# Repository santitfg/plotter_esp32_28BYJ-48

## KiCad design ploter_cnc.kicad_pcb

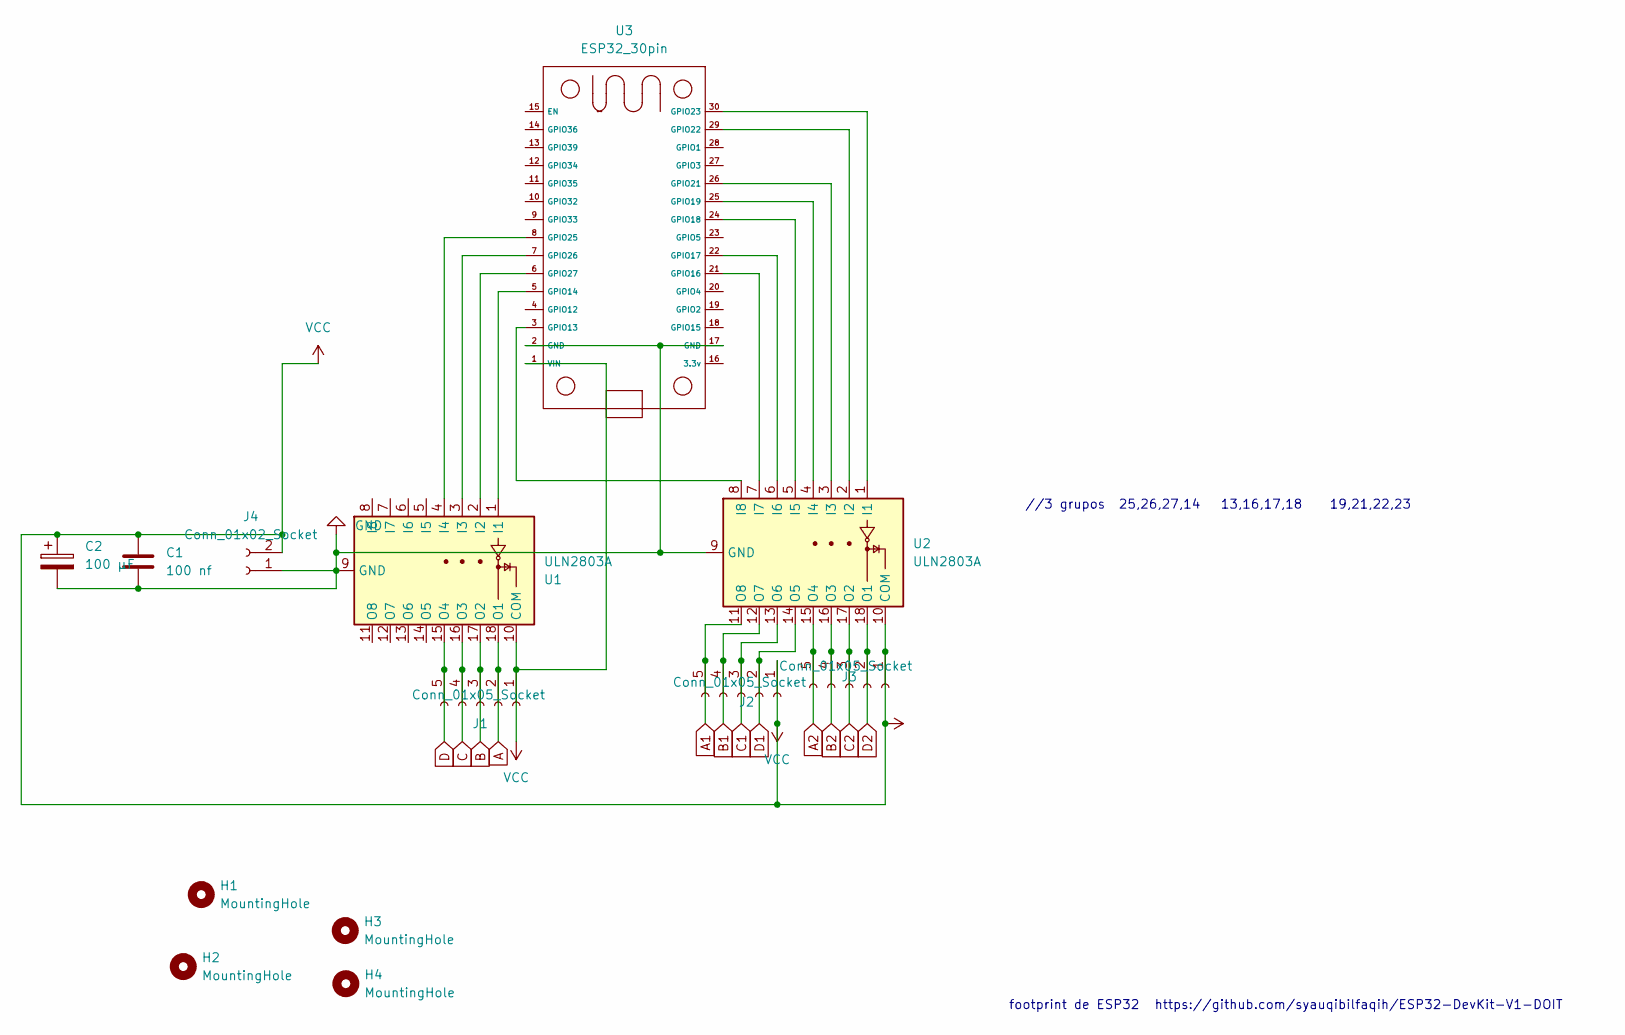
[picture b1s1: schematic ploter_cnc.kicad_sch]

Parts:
C1: 100 nf; C_Disc_D4.3mm_W1.9mm_P5.00mm
C2: 100 µF; CP_Radial_D4.0mm_P2.00mm
H1, H2, H3, H4: MountingHole; MountingHole_2.2mm_M2_DIN965_Pad
J1, J2, J3: Conn_01x05_Socket; Molex_KK-254_AE-6410-05A_1x05_P2.54mm_Vertical
J4: Conn_01x02_Socket; Molex_KK-254_AE-6410-02A_1x02_P2.54mm_Vertical
U1, U2: ULN2803A; DIP-18_W7.62mm_Socket_LongPads
U3: ESP32_30pin

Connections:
A: J1.2, U1.18 (O1)
A2: J3.5, U2.15 (O4)
B: J1.3, U1.17 (O2)
B2: J3.4, U2.16 (O3)
C: J1.4, U1.16 (O3)
C2: J3.3, U2.17 (O2)
D: J1.5, U1.15 (O4)
D2: J3.2, U2.18 (O1)
GND: C1.2, C2.2, J4.1, U1.9 (GND), U2.9 (GND), U3.2 (GND), U3.17 (GND)
unnamed: J2.2, U2.14 (O5)
unnamed: J2.3, U2.13 (O6)
unnamed: J2.4, U2.12 (O7)
unnamed: J2.5, U2.11 (O8)
unnamed: U1.1 (I1), U3.5 (GPIO14)
unnamed: U1.2 (I2), U3.6 (GPIO27)
unnamed: U1.3 (I3), U3.7 (GPIO26)
unnamed: U1.4 (I4), U3.8 (GPIO25)
unnamed: U2.1 (I1), U3.30 (GPIO23)
unnamed: U2.2 (I2), U3.29 (GPIO22)
unnamed: U2.3 (I3), U3.26 (GPIO21)
unnamed: U2.4 (I4), U3.25 (GPIO19)
unnamed: U2.5 (I5), U3.24 (GPIO18)
unnamed: U2.6 (I6), U3.22 (GPIO17)
unnamed: U2.7 (I7), U3.21 (GPIO16)
unnamed: U2.8 (I8), U3.3 (GPIO13)
VCC: C1.1, C2.1, J1.1, J2.1, J3.1, J4.2, U1.10 (COM), U2.10 (COM), U3.1 (VIN)

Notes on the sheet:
https://github.com/syauqibilfaqih/ESP32-DevKit-V1-DOIT
//3 grupos 25,26,27,14 13,16,17,18 19,21,22,23
footprint de ESP32

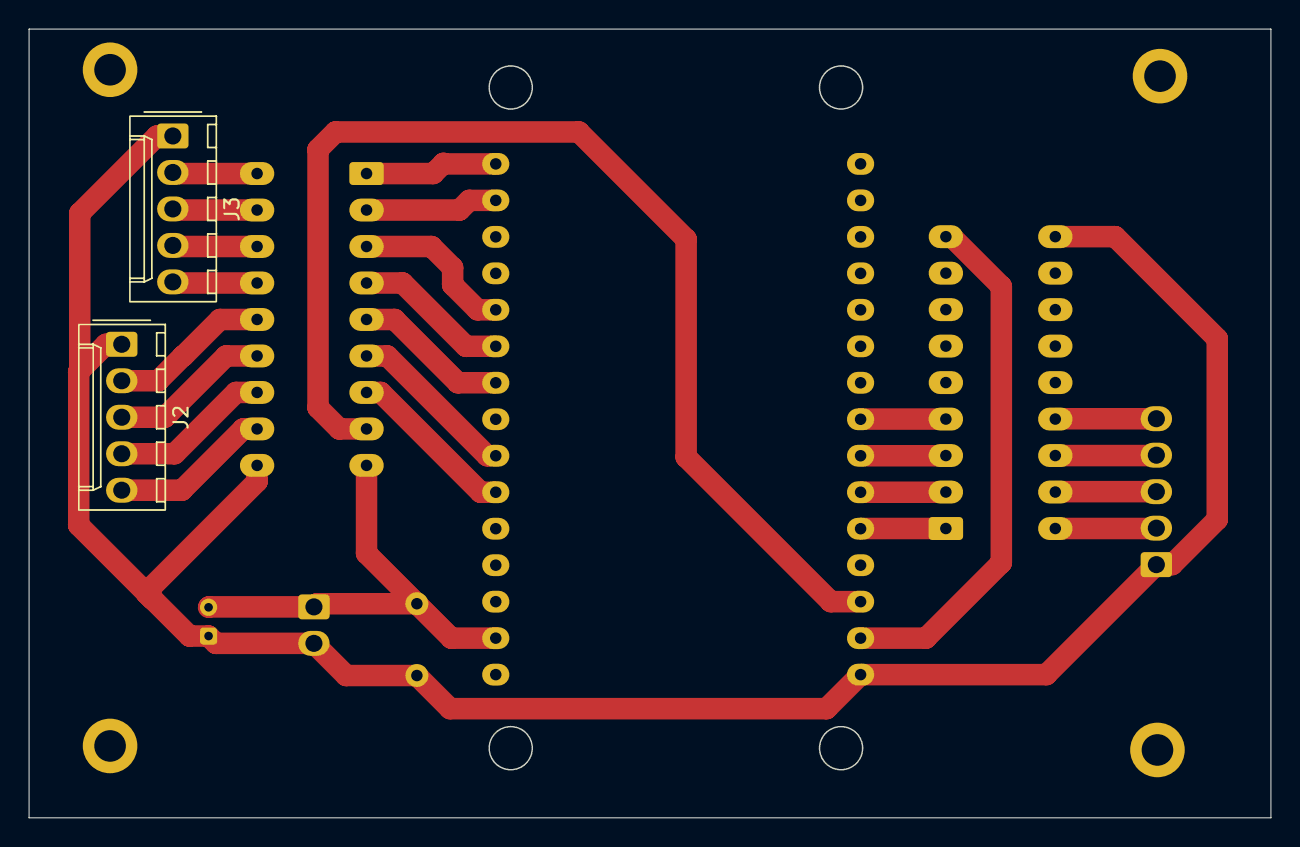
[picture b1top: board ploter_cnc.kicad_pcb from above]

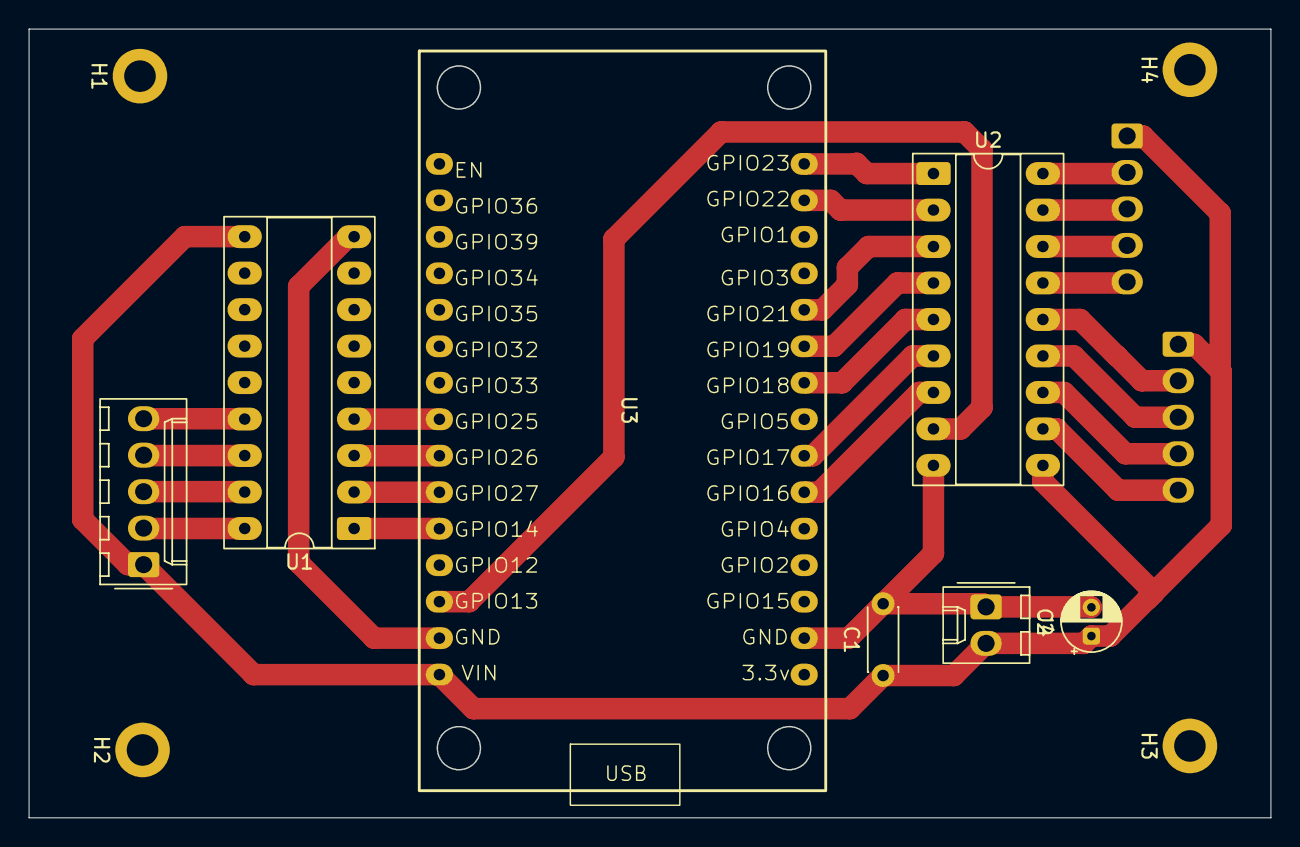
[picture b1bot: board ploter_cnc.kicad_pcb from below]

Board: 2 copper layers, 86.5 x 54.9 mm, 13 parts (11 on the bottom side), 26 nets.
